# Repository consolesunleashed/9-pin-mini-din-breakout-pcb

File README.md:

Working on designs to release for free can be both time consuming and expensive. If you like what I do, a small donation will go a long way in helping me continue to serve the modding community as best as I can, with many more free and original guides, designs, and ideas to come.

# 9-Pin Mini DIN Breakout PCB

A simple 9-Pin Mini DIN breakout PCB for AV modding consoles. Uses standard Sega Mega Drive 2 signal routing. Features a jumper to combine left and right audio channels, and a jumper to send the left audio channel, or both, to the mono audio pin. It's about as good as a 9-Pin Mini DIN breakout PCB could be.

## Manufacturing

- 1mm is perfect.

## Version History

9-Pin Mini DIN Breakout PCB v1 - 23/07/2022

## License

If you use this in any way, shape or form, you must include a link back to this repository and mention me by name on any sales pages and social media posts. Not only will this help me to keep designing mod kits and offering them to the community, but it is basic common courtesy as well. Don't be a douchebag. :)

Also this 'GNU GENERAL PUBLIC LICENSE Version 2, June 1991'.

## Donate

Working on designs to release for free can be both time consuming and expensive. If you like what I do, a small donation will go a long way in helping me continue to serve the modding community as best as I can, with many more free and original guides, designs, and ideas to come.

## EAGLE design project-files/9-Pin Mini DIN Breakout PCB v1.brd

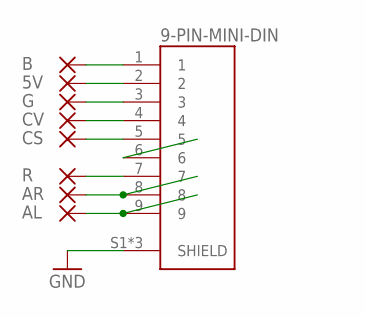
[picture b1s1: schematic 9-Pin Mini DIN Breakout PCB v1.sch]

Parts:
5V: PADSRECTANGLE-1,27X2,54; RECTANGLE-1,27X2,54
9-PIN-MINI-DIN: 9-PIN-MINI-DIN
AL: PADSRECTANGLE-1,27X2,54; RECTANGLE-1,27X2,54
AR: PADSRECTANGLE-1,27X2,54; RECTANGLE-1,27X2,54
B: PADSRECTANGLE-1,27X2,54; RECTANGLE-1,27X2,54
CS: PADSRECTANGLE-1,27X2,54; RECTANGLE-1,27X2,54
CV: PADSRECTANGLE-1,27X2,54; RECTANGLE-1,27X2,54
G: PADSRECTANGLE-1,27X2,54; RECTANGLE-1,27X2,54
R: PADSRECTANGLE-1,27X2,54; RECTANGLE-1,27X2,54

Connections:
5V: 5V.1, 9-PIN-MINI-DIN.2
AL: 9-PIN-MINI-DIN.9, AL.1
AM: 9-PIN-MINI-DIN.6
AR: 9-PIN-MINI-DIN.8, AR.1
B: 9-PIN-MINI-DIN.1, B.1
CS: 9-PIN-MINI-DIN.5, CS.1
CV: 9-PIN-MINI-DIN.4, CV.1
G: 9-PIN-MINI-DIN.3, G.1
GND: 9-PIN-MINI-DIN.S1 (SHIELD), 9-PIN-MINI-DIN.S2 (SHIELD), 9-PIN-MINI-DIN.S3 (SHIELD)
R: 9-PIN-MINI-DIN.7, R.1

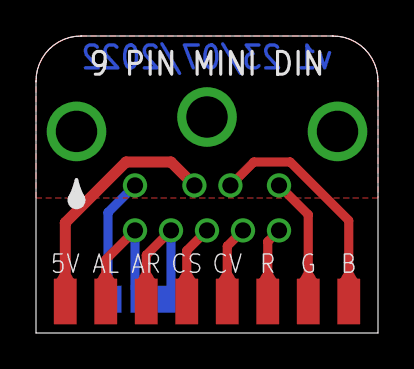
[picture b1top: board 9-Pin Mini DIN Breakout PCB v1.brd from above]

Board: 2 copper layers, 19.0 x 16.5 mm, 9 parts (1 on the bottom side), 9 nets.
